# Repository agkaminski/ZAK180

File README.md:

# ZAK180 computer

## Hardware features

- Z180 CPU,
- 1 MB of static RAM,
- 16 KB bootloader ROM,
- Floppy disk drive,
- 16 bit GPIO user port,
- 2 UARTs: USB-C and RS232,
- AY-3-8912 sound,
- 80x60 B&W text mode VGA output,
- custom Cherry-MX mechanical keyboard,
- USB-C powered.

## Firmare

ZAKOS code repository is located [here](https://github.com/agkaminski/ZAKOS).

## Memory map

| Start   | End     | Description                              |
|---------|---------|------------------------------------------|
| 0x00000 | 0x03FFF | ROM, disabled after boot, after that RAM |
| 0x04000 | 0xFDFFF | RAM                                      |
| 0xFE000 | 0xFFFFF | Memory mapped I/O, VGA VRAM              |

## I/O map

8-bit I/O is used.

| Start | End  | Description             |
|-------|------|-------------------------|
| 0x00  | 0x3F | Z180 internal I/O       |
| 0x40  | 0x5F | VBLANK IRQ acknowledge  |
| 0x60  | 0x7F | ROM disable control     |
| 0x80  | 0x9F | Keyboard                |
| 0xA0  | 0xBF | Z80 PIO (user port)     |
| 0xC0  | 0xDF | AY-3-8912               |
| 0xE0  | 0xFF | 82077 floppy controller |

## Repository structure

### datasheet

Collection of useful datasheets, might be removed in the future.

### keyboard2

Subrepository that contains a hardware project of a mechanical keyboard for the
computer.

### kicad

KiCAD project of the computer's PCB.

### vga

HDL of the VGA timing generator implemented in a XC9536 CPLD, tool to generate
font ROM.

### schematic.pdf

Schematic of the computer in a friendly .pdf form.

### 3dprint

3D models designed for FDM priting.

## License

[Attribution-NonCommercial 4.0](LICENSE)

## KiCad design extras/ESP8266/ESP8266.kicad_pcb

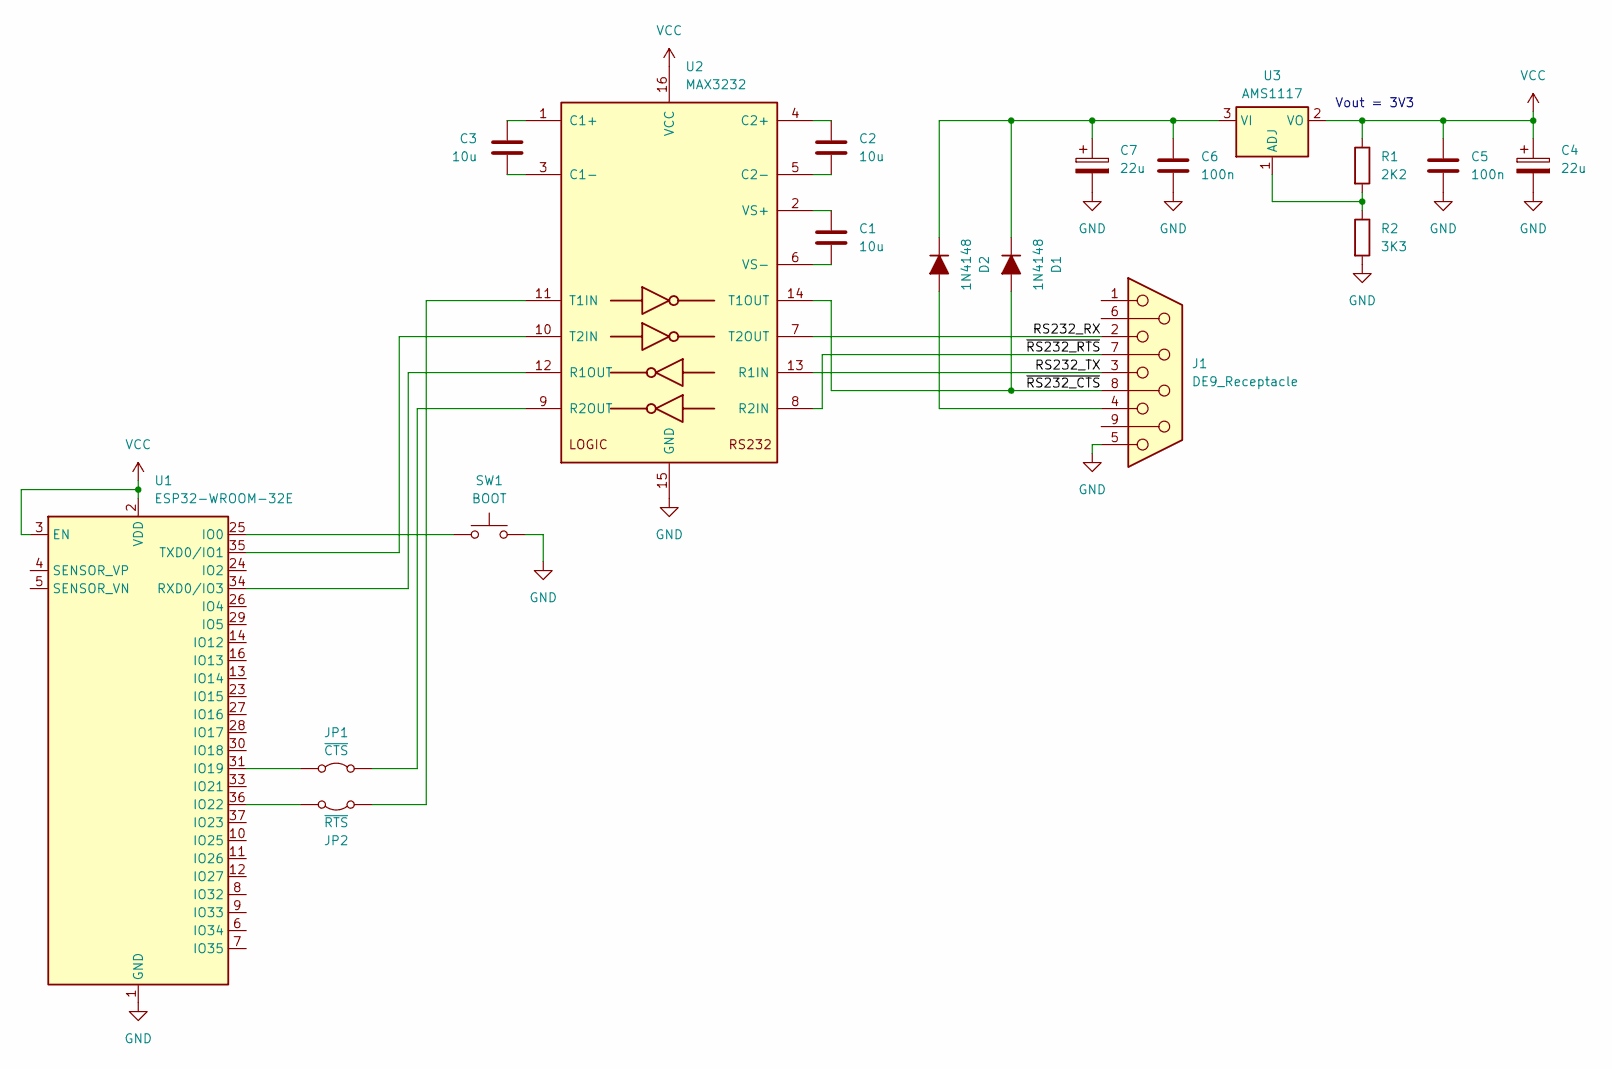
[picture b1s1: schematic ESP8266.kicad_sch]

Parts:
C1, C2, C3: 10u; C_0805_2012Metric_Pad1.18x1.45mm_HandSolder
C4, C7: 22u; CP_EIA-3528-15_AVX-H_Pad1.50x2.35mm_HandSolder
C5, C6: 100n; C_0805_2012Metric_Pad1.18x1.45mm_HandSolder
D1, D2: 1N4148; D_MiniMELF
J1: DE9_Receptacle; DSUB-9_Female_EdgeMount_P2.77mm
JP1: ~{CTS}; SolderJumper-2_P1.3mm_Bridged_RoundedPad1.0x1.5mm
JP2: ~{RTS}; SolderJumper-2_P1.3mm_Bridged_RoundedPad1.0x1.5mm
R1: 2K2; R_0805_2012Metric_Pad1.15x1.40mm_HandSolder
R2: 3K3; R_0805_2012Metric_Pad1.15x1.40mm_HandSolder
SW1: BOOT; SW_SPST_PTS645
U1: ESP32-WROOM-32E; ESP32-WROOM-32D
U2: MAX3232; SOP-16_4.4x10.4mm_P1.27mm
U3: AMS1117; SOT-223-3_TabPin2

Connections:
/RS232_RX: J1.2, U2.7 (T2OUT)
/RS232_TX: J1.3, U2.13 (R1IN)
/~RS232_CTS: D1.2 (A), J1.8, U2.14 (T1OUT)
/~RS232_RTS: J1.7, U2.8 (R2IN)
GND: C4.2, C5.2, C6.2, C7.2, J1.5, R2.2, SW1.2, U1.1 (GND), U1.15 (GND), U1.38 (GND), U1.39 (GND), U2.15 (GND)
unnamed: C6.1, C7.1, D1.1 (K), D2.1 (K), U3.3 (VI)
unnamed: D2.2 (A), J1.4
unnamed: JP1.1 (A), U1.31 (IO19)
unnamed: JP1.2 (B), U2.9 (R2OUT)
unnamed: JP2.1 (A), U1.36 (IO22)
unnamed: JP2.2 (B), U2.11 (T1IN)
unnamed: SW1.1, U1.25 (IO0)
unnamed: U1.34 (RXD0/IO3), U2.12 (R1OUT)
unnamed: U1.35 (TXD0/IO1), U2.10 (T2IN)
unnamed: C3.2, U2.1 (C1+)
unnamed: C3.1, U2.3 (C1-)
unnamed: C2.1, U2.4 (C2+)
unnamed: C2.2, U2.5 (C2-)
unnamed: C1.1, U2.2 (VS+)
unnamed: C1.2, U2.6 (VS-)
unnamed: R1.2, R2.1, U3.1 (ADJ)
VCC: C4.1, C5.1, R1.1, U1.2 (VDD), U1.3 (EN), U2.16 (VCC), U3.2 (VO)

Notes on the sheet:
Vout = 3V3

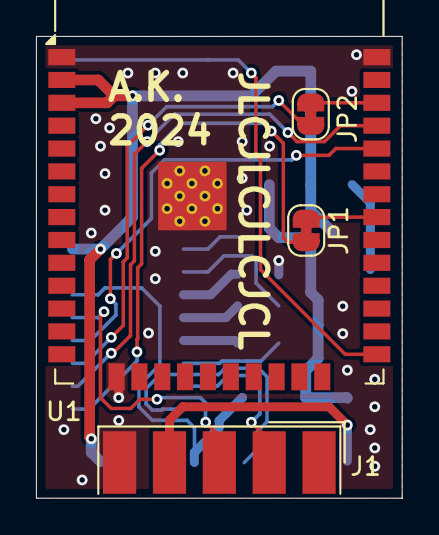
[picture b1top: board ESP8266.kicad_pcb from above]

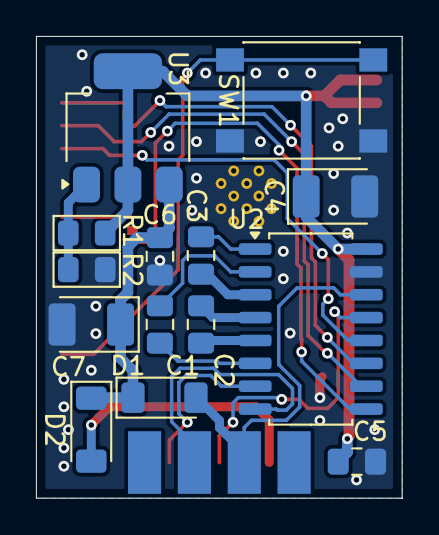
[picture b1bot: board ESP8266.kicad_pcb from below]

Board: 2 copper layers, 20.3 x 25.7 mm, 18 parts (14 on the bottom side), 22 nets.

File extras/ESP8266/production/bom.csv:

Designator,Footprint,Quantity,Value,LCSC Part #
"C1, C2, C3",0805,3,10u,
"C4, C7",CP_EIA-3528-15_AVX-H_Pad1.50x2.35mm_HandSolder,2,22u,
"C5, C6",0805,2,100n,
"D1, D2",D_MiniMELF,2,1N4148,
J1,DSUB-9_Female_EdgeMount_P2.77mm,1,DE9_Receptacle,
JP1,SolderJumper-2_P1.3mm_Bridged_RoundedPad1.0x1.5mm,1,~{CTS},
JP2,SolderJumper-2_P1.3mm_Bridged_RoundedPad1.0x1.5mm,1,~{RTS},
R1,0805,1,2K2,
R2,0805,1,3K3,
SW1,SW_SPST_PTS645,1,BOOT,
U1,ESP32-WROOM-32D,1,ESP32-WROOM-32E,
U2,SOP-16_4.4x10.4mm_P1.27mm,1,MAX3232,
U3,SOT-223-3_TabPin2,1,AMS1117,

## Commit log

2024-08-20 Add README and LICENSE
2024-08-20 Add keyboard submodule
2024-08-29 FW: start work on drivers
2024-08-29 HW: Fix UART1 having RX and TX swapped
2024-08-29 FW: Add simple dead/alive test (crasm)
2024-08-29 Update README and issues
2024-08-30 FW: Bootloader makefile
2024-08-30 Bootloader: start work on bootstrap
2024-08-30 HW: Fix bug in I/O decoder
2024-08-30 Drivers: Add makefile, fix AY-3-8912
2024-08-30 bootloader: Working bootstrap to high RAM
2024-08-30 bootloader: working .data and .bss init
2024-08-30 driver: Start work on floppy controller driver
2024-08-30 schematic: Fix incorrect information about 82077 mode
2024-08-31 driver: working floppy sector read
2024-08-31 driver/floppy: slight cleanup
2024-08-31 driver/floppy: improve error handling
2024-08-31 driver/floppy: refactor
2024-08-31 driver/floppy: Working read and write
2024-08-31 driver/floppy: Rename lower layer, working access to the whole disk
2024-08-31 driver: add PIO driver
2024-08-31 driver/floppy: add floppy interface wrapers
2024-08-31 driver/floppy: remove redundant seek
2024-08-31 filesystem: start work on FAT12
2024-09-01 driver/floppy: optimize FIFO read/write, add timeout
2024-09-01 driver/floppy: fix buggy retval check
2024-09-01 driver/floppy: Fix build, use asm local labels
2024-09-01 driver/floppy: add comment about not working eject detection, change delay
2024-09-01 driver/floppy: remove explicit RET
2024-09-01 filesystem: Working FAT entry getter
2024-09-01 FAT12: optimize sector re-access, update FAT copy on write
2024-09-01 driver/floppy: Fix write regression
2024-09-01 FAT12: working FAT set
2024-09-01 bootloader: slight cleanup
2024-09-01 FAT12: start work on file read
2024-09-01 Make build system slightly less lousy
2024-09-01 FAT12: start work on open
2024-09-02 FAT12: Working file open and read
2024-09-02 floppy: Fix disk change detection
2024-09-02 HW: remove unnecessary kicad files
2024-09-02 FAT12: start work on truncate
2024-09-02 FAT12: working truncate to smaller
2024-09-02 FAT12: working truncate to bigger size
2024-09-02 FAT12: working file write
2024-09-02 FAT12: fix truncate for non-changing cluster count
2024-09-04 FW: Add interrupts handling in bootloader
2024-09-05 Bootloader: relocate bootloader to common 1 to make bank area coherently scratchpad
2024-09-07 driver: start work on VGA
2024-09-07 vga: mostly working vga driver
2024-09-08 HW: Fix A0 of AY-3-8912 being connected to D0 instead of A0
2024-09-08 VGA: working VGA
2024-09-08 VGA: remove dead variables
2024-09-08 VGA: new approach - double buffered partial refresh
2024-09-08 VGA: re-add cursor
2024-09-08 VGA: put vga_set in critical section
2024-09-08 VGA: Add description and put vga_clear in critical section
2024-09-08 bootloader: Working kernel load
2024-09-09 FW: Enable SDCC optimizations
2024-09-09 FAT12: Fix UB in file_read preventing reads over 512 bytes
2024-09-09 bootloader: add memtest
2024-09-09 FAT12: Simplify file_write
2024-09-09 Remove redundant file
2024-09-09 Update schematic pdf file
2024-09-09 Add devkit STL model
2024-09-09 Add memory maps to README
2024-09-10 HW: Fix address and data buses being swapped for keyboard connector
2024-09-10 HW: update schematic pdf
2024-09-10 HW: Connect 82077 /DREQ to the Z180 DMA ch 1, PCB decorations
    Rev B done
2024-09-11 UART: use interrupts
2024-09-12 FAT12: Separate read file and dir, use errno
2024-09-14 Kernel: Initial memory management
2024-09-14 UART: Fix warning
2024-09-14 Kernel: Working linear memory alloc/free
2024-09-14 kernel/memory: working split/merge
2024-09-14 kernel/memory: remove debug
2024-09-14 kernel: working systick timer
2024-09-14 kernel: save/restore MMU context
2024-09-15 kernel: start work on threads
2024-09-15 kernel: working scheduler
2024-09-16 kernel: working thread sleep
2024-09-16 kernel: add lock and condvar
2024-09-16 kernel: yield on lock unlock
2024-09-16 kernel: change code structure
2024-09-16 fw: fix header paths
2024-09-16 kernel/makefile: fix clean
2024-09-16 fw: move list to lib
2024-09-16 kernel: remove redundant file
2024-09-16 kernel/proc: fix incorrect version of timer_get being used
2024-09-16 Replace irq disable with scheduler lock. Make critical section not enabled on boot
2024-09-16 VGA: fix wrong version of vga_set being used
2024-09-17 VGA: optimize IRQ
2024-09-17 kernel: start work on FS abstraction
2024-09-17 memory: import kmalloc
2024-09-17 kernel: add kmalloc and condwait tests
2024-09-17 VGA: guard against cursor handling in the interrupt
2024-09-17 VGA: handle tab
2024-09-22 HW: Fix unconnected /SOUND net, add /RST header and /DTR power supply
2024-09-22 test: optimize kmalloc test
2024-09-22 HW: revision C
2024-10-10 HW: remove rev A gerbers
2024-10-10 HW: add ESP32 dongle
2024-10-10 Update photos
2024-10-24 driver: compile all drivers to the single lib
2024-10-24 FAT: start work on a'la vfs FAT implementation (WIP)
2024-12-14 kernel: define block device API + floopy blk
2024-12-14 vfs: start vfs API implementation (WIP)
2024-12-14 blk: fix sync size type in API
2024-12-14 vfs: improve API, mount implementation
2024-12-15 vfs: partial fs API implementation
2024-12-15 fs: use blk interface in FAT, remove adhoc one. Build fix
2024-12-15 kernel: fix makefile clean
2024-12-15 lib: add panic()
2024-12-15 vfs: finish basic vfs API
2024-12-15 dev: fix floppy blk argument types
2024-12-15 dev: fix floppy pseud-cache thining it has read sector #0
2024-12-15 fat: fix BPB check
2024-12-15 kernel: mount rootfs
2024-12-16 kernel: fix sleep value (ms, not us)
2024-12-16 mem: change assumption to assert
2024-12-16 fs: init locks (not strictly needed when lock is zeroed-out)
2025-01-11 3D: add case 3D model (FreeCAD + STL)
2025-01-12 3D: improve case model
2025-01-12 3D/case: add vent holes, move PCB to clear IO plugs
2025-01-13 3D: fix bottom no longer matching case, move it to the one FreeCAD file
2025-01-19 fs: remove dentry from file node, add FAT cache
2025-01-19 fs: fix mount regression
2025-04-03 file: optimise file_dup2
2025-06-21 README: fix typo
2025-06-29 vga/cpld: fix wrong .v file, add .jed
